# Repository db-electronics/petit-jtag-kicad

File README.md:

# Petit JTAG
Petit JTAG is a USB Blaster adapter which reduces the 2x5 100mil connector to a 1x6 2mm connector when space is constrained on the target PCB. It also has a type B USB input to provide power to the target board from either VBUS 5V or 3.3V from an onboard voltage regulator. This is selectable via pin header.

# Support Open Source
If you're going to use my free projects please consider sponsoring my work. Thanks!

- [Github Sponsor](https://github.com/sponsors/db-electronics)
- [Pateron](https://patreon.com/dbelectronics)

# Changelog
- [v1.1](https://github.com/db-electronics/petit-jtag-kicad/releases/tag/v1.1)
  - change 2x3 50mil to a 1x6 2mm staggered footprint for more consistent connection to target board
- [v1.0](https://github.com/db-electronics/petit-jtag-kicad/releases/tag/v1.0)
  - initial release

# Copyright and Disclaimer
Copyright: René Richard

This documentation describes Open Hardware and is licensed under the
CERN OHL v. 1.2.

You may redistribute and modify this documentation under the terms of the
CERN OHL v.1.2. (http://ohwr.org/cernohl). This documentation is distributed
WITHOUT ANY EXPRESS OR IMPLIED WARRANTY, INCLUDING OF
MERCHANTABILITY, SATISFACTORY QUALITY AND FITNESS FOR A
PARTICULAR PURPOSE. Please see the CERN OHL v.1.2 for applicable
conditions

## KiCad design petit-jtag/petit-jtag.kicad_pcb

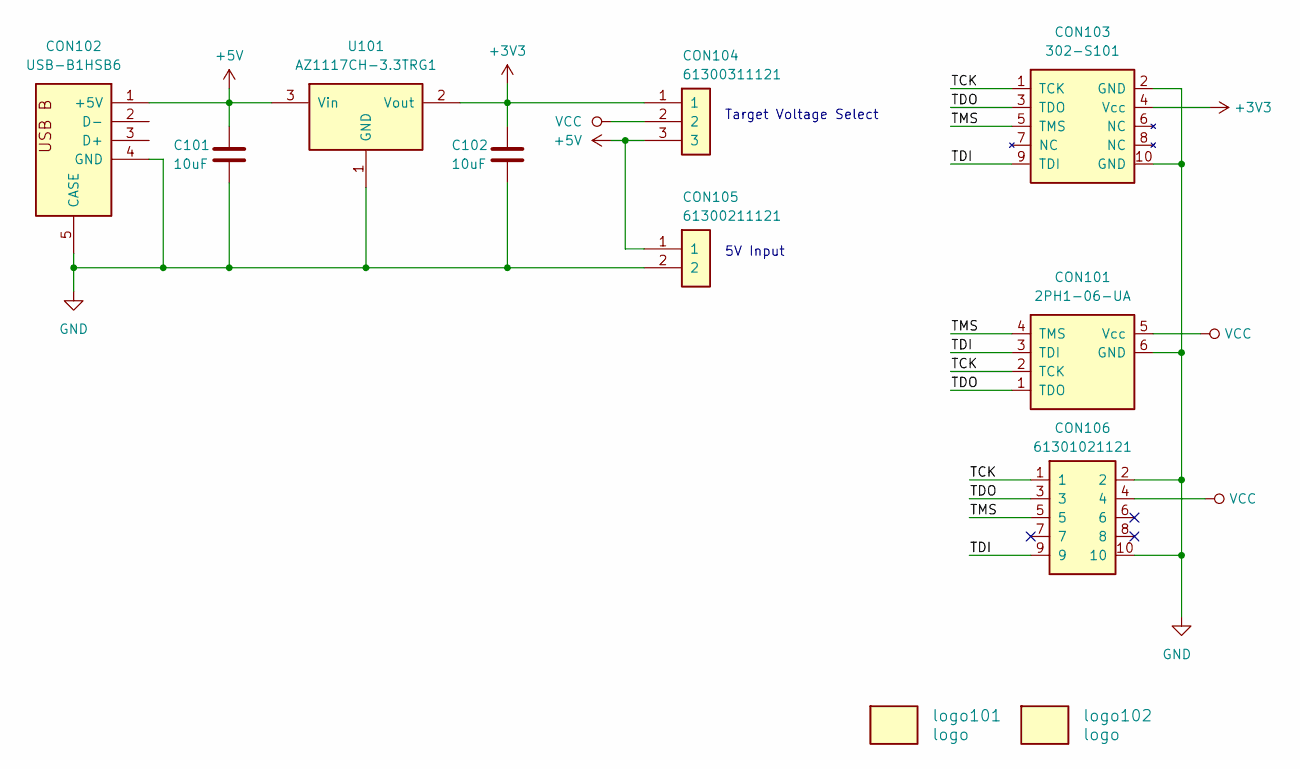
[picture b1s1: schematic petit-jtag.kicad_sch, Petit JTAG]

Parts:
C101, C102: 10uF; 0805
CON101: 2PH1-06-UA; HDR1X6_2MM
CON102: USB-B1HSB6; USB-B1HSxx
CON103: 302-S101; HDR2X5-JTAG_SHROUD
CON104: 61300311121; HDR1X3
CON105: 61300211121; HDR1X2
CON106: 61301021121; HDR2X5-JTAG
U101: AZ1117CH-3.3TRG1; SOT-223
logo101: logo; db-logo_7.5mm
logo102: logo; oshw-logo_5mm

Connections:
+3V3: C102.1, CON103.4 (Vcc), CON104.1, U101.2 (Vout)
+5V: C101.1, CON102.1 (+5V), CON104.3, CON105.1, U101.3 (Vin)
/TCK: CON101.2 (TCK), CON103.1 (TCK), CON106.1
/TDI: CON101.3 (TDI), CON103.9 (TDI), CON106.9
/TDO: CON101.1 (TDO), CON103.3 (TDO), CON106.3
/TMS: CON101.4 (TMS), CON103.5 (TMS), CON106.5
GND: C101.2, C102.2, CON101.6 (GND), CON102.4 (GND), CON102.5 (CASE), CON103.2 (GND), CON103.10 (GND), CON105.2, CON106.2, CON106.10, U101.1 (GND)
VCC: CON101.5 (Vcc), CON104.2, CON106.4

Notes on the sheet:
Target Voltage Select
5V Input

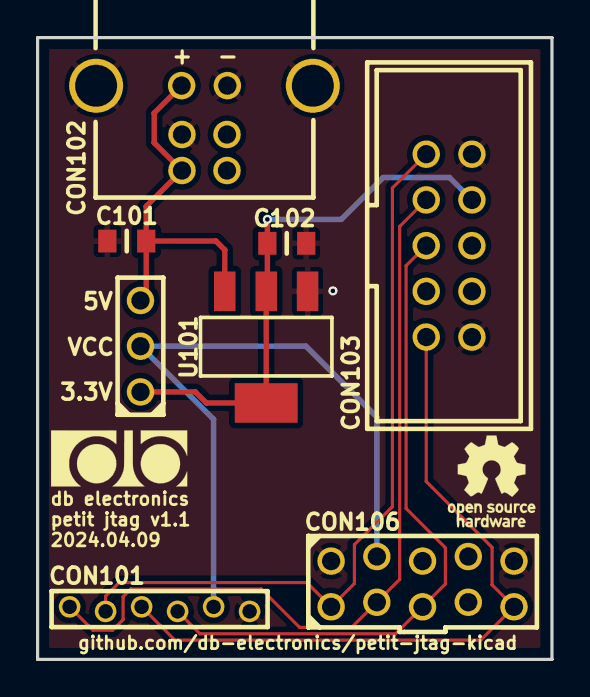
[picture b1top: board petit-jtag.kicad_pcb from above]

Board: 2 copper layers, 28.6 x 34.5 mm, 11 parts (0 on the bottom side), 8 nets.

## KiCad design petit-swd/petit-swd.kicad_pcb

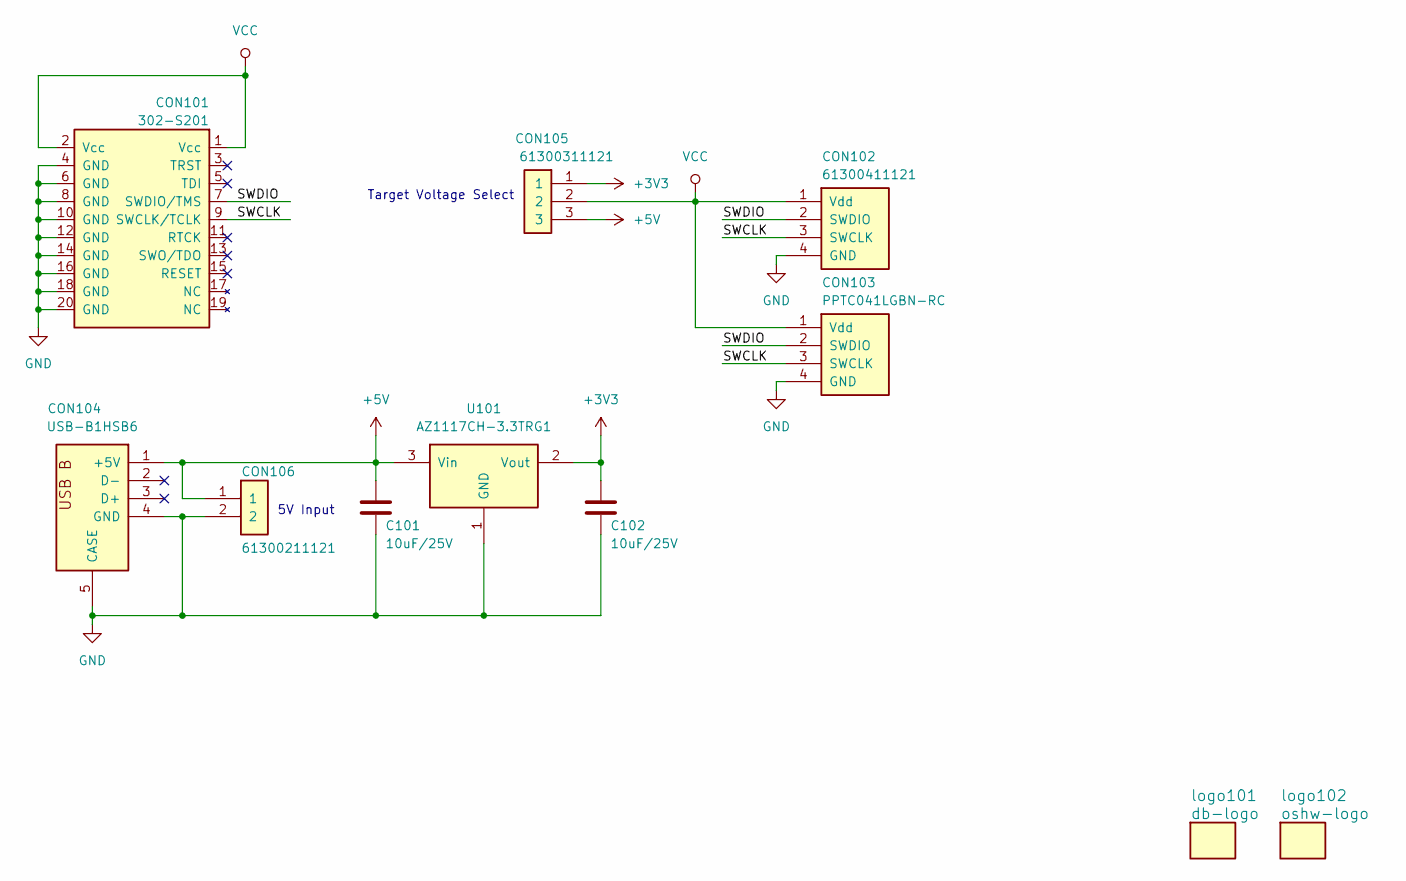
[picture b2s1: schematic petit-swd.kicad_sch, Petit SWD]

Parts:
C101, C102: 10uF/25V; 0805
CON101: 302-S201; HDR2X10-JTAG-SHROUD
CON102: 61300411121; HDR1X4
CON103: PPTC041LGBN-RC; RCP1X4_RA
CON104: USB-B1HSB6; USB-B1HSxx
CON105: 61300311121; HDR1X3
CON106: 61300211121; HDR1X2
U101: AZ1117CH-3.3TRG1; SOT-223; Digikey AZ1117CH-3.3TRG1DICT-ND
logo101: db-logo; db-logo_10mm
logo102: oshw-logo; oshw-logo_7.5mm

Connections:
+3V3: C102.1, CON105.1, U101.2 (Vout)
+5V: C101.1, CON104.1 (+5V), CON105.3, CON106.1, U101.3 (Vin)
/SWCLK: CON101.9 (SWCLK/TCLK), CON102.3 (SWCLK), CON103.3 (SWCLK)
/SWDIO: CON101.7 (SWDIO/TMS), CON102.2 (SWDIO), CON103.2 (SWDIO)
GND: C101.2, C102.2, CON101.4 (GND), CON101.6 (GND), CON101.8 (GND), CON101.10 (GND), CON101.12 (GND), CON101.14 (GND), CON101.16 (GND), CON101.18 (GND), CON101.20 (GND), CON102.4 (GND), CON103.4 (GND), CON104.4 (GND), CON104.5 (CASE), CON106.2, U101.1 (GND)
VCC: CON101.1 (Vcc), CON101.2 (Vcc), CON102.1 (Vdd), CON103.1 (Vdd), CON105.2

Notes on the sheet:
Target Voltage Select
5V Input

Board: 2 copper layers, 11 parts (0 on the bottom side), 6 nets, no tracks yet.

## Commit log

2023-12-28 initial file commiut
2023-12-29 mostly done v1.0
2023-12-29 version 1.0 ready
2023-12-29 add output files for v1.0
2023-12-29 added bom file
2023-12-29 quick readme
2024-04-05 updated with new staggered pin headers instead of 2x3
2024-04-08 petit-swd board
2024-04-08 added funding.yml
2024-04-10 swd v1.0 sch complete, jtag v1.1 files
2024-04-10 separate petit-swd into its own repo
2024-04-10 version 1.1 files ready
2024-04-10 version 1.1 files ready, now

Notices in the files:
petit-jtag/petit-jtag.kicad_pcb:
Licensed under CERN OHL v.1.2
Copyright René Richard 2024
petit-swd/petit-swd.kicad_pcb:
Copyright 2024 René Richard
